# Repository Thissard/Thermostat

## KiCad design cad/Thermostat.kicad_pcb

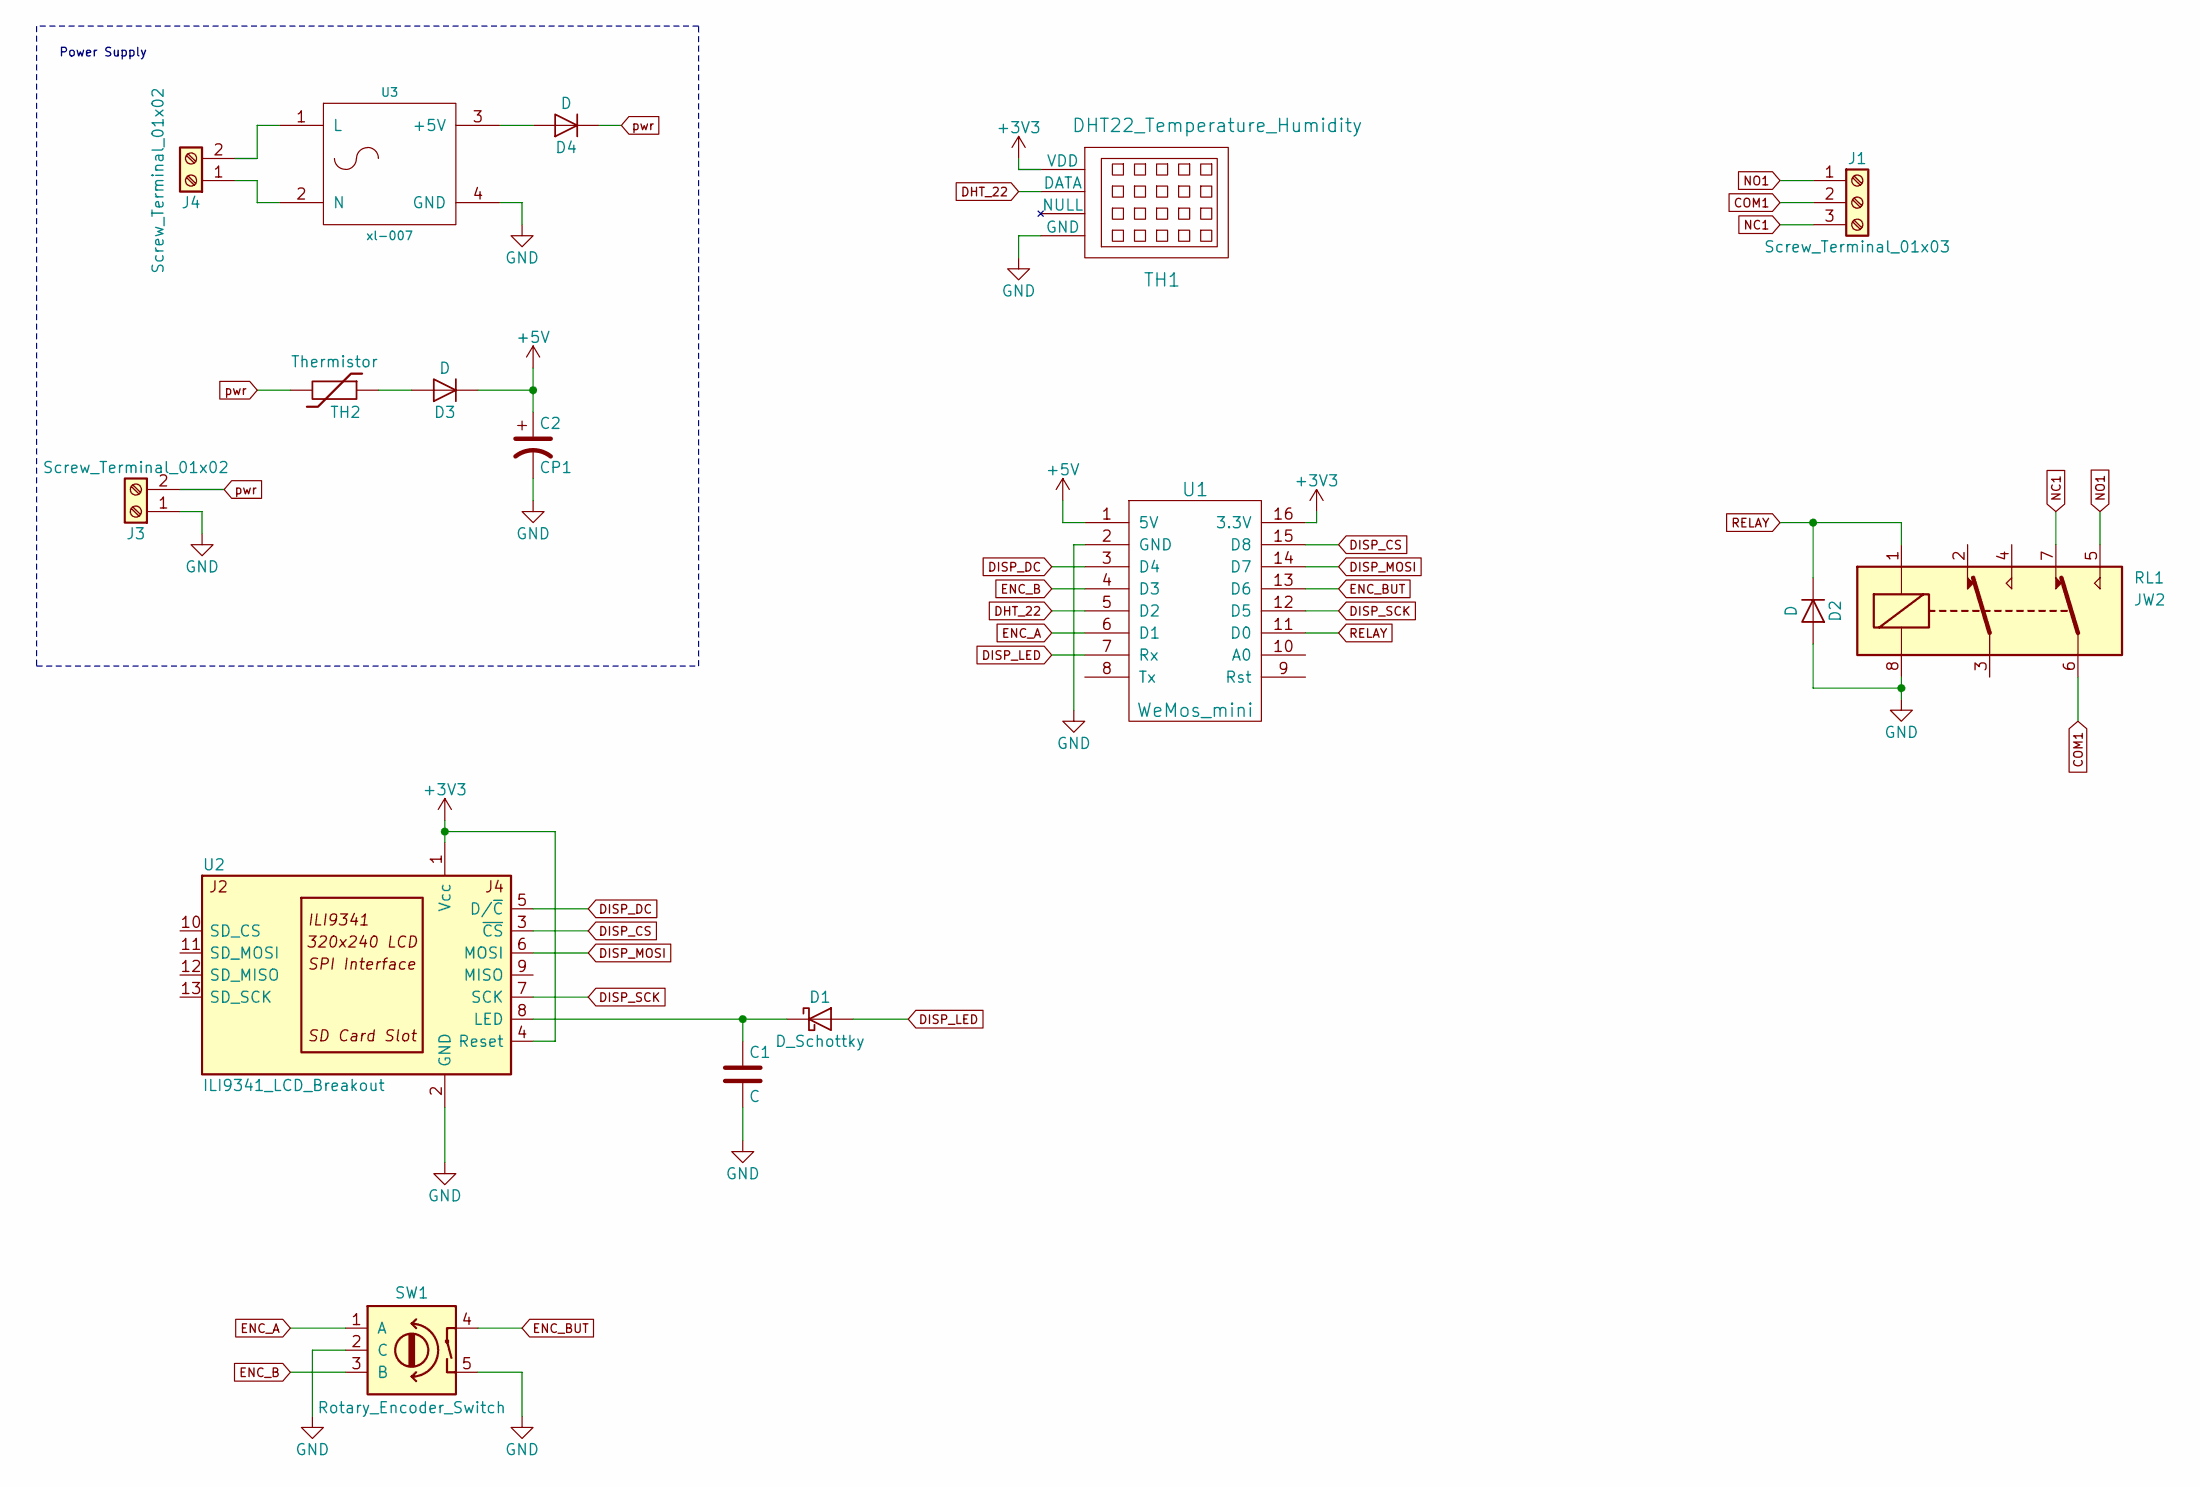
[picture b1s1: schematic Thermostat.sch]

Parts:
C1: C; Resistor_SMD+THTuniversal_0805to2512_HandSoldering
C2: CP1; Resistor_SMD+THTuniversal_0805to2512_HandSoldering
D1: D_Schottky; Resistor_SMD+THTuniversal_0805to2512_HandSoldering
D2, D3, D4: D; Resistor_SMD+THTuniversal_0805to2512_HandSoldering
J1: Screw_Terminal_01x03; PhoenixContact_MC-GF_03x5.08mm_Angled_ThreadedFlange
J3, J4: Screw_Terminal_01x02; PhoenixContact_MC-GF_02x5.08mm_Angled_ThreadedFlange
RL1: JW2; Relay_DPDT_Omron_G5V-2
SW1: Rotary_Encoder_Switch; SF-ROTARY-ENCODER
TH1: DHT22_Temperature_Humidity
TH2: Thermistor; Resistor_SMD+THTuniversal_0805to2512_HandSoldering
U1: WeMos_mini; D1_mini_board
U2: ILI9341_LCD_Breakout; ILI9431 2,8 TFT
U3: xl-007; xl007

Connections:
+3V3: TH1.1 (VDD), U1.16 (3.3V), U2.1 (Vcc), U2.4 (Reset)
+5V: C2.1, D3.1 (K), U1.1 (5V)
COM1: J1.2, RL1.6
DHT_22: TH1.2 (DATA), U1.5 (D2)
DISP_CS: U1.15 (D8), U2.3 (~CS)
DISP_DC: U1.3 (D4), U2.5 (D/~C)
DISP_LED: D1.2 (A), U1.7 (Rx)
DISP_MOSI: U1.14 (D7), U2.6 (MOSI)
DISP_SCK: U1.12 (D5), U2.7 (SCK)
ENC_A: SW1.1 (A), U1.6 (D1)
ENC_B: SW1.3 (B), U1.4 (D3)
ENC_BUT: SW1.4, U1.13 (D6)
GND: C1.2, C2.2, D2.2 (A), J3.1, RL1.8, SW1.2 (C), SW1.5, TH1.4 (GND), U1.2 (GND), U2.2 (GND), U3.4 (GND)
NC1: J1.3, RL1.7
NO1: J1.1, RL1.5
unnamed: C1.1, D1.1 (K), U2.8 (LED)
unnamed: D3.2 (A), TH2.1
unnamed: D4.2 (A), U3.3 (+5V)
unnamed: J4.1, U3.2 (N)
unnamed: J4.2, U3.1 (L)
RELAY: D2.1 (K), RL1.1, U1.11 (D0)
pwr: D4.1 (K), J3.2, TH2.2

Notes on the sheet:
Power Supply

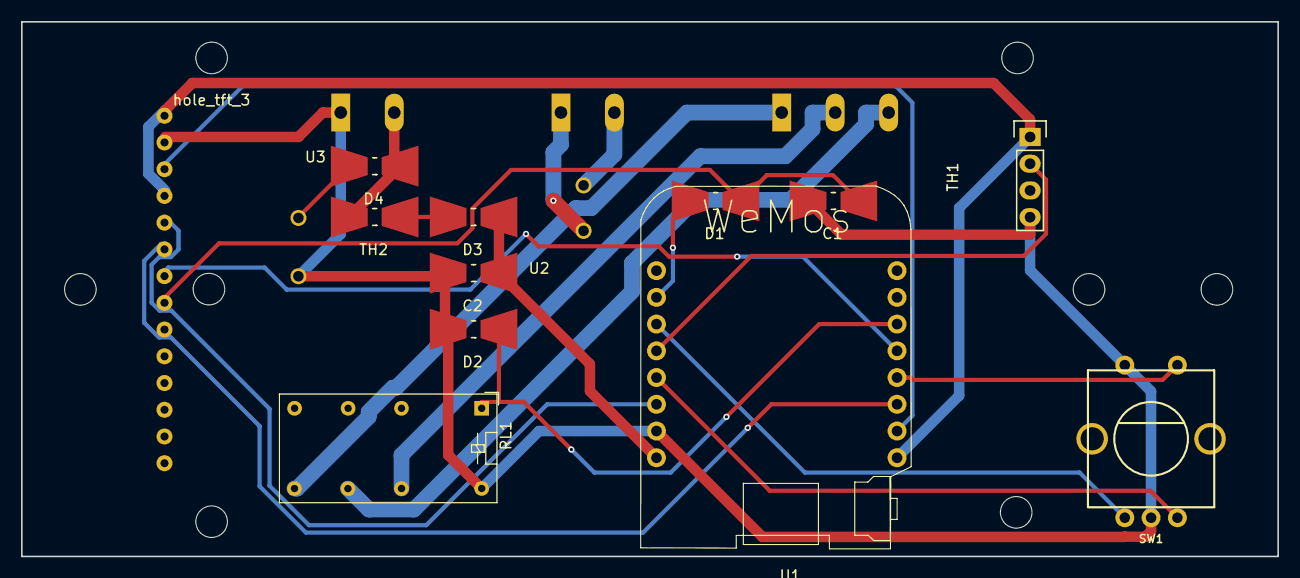
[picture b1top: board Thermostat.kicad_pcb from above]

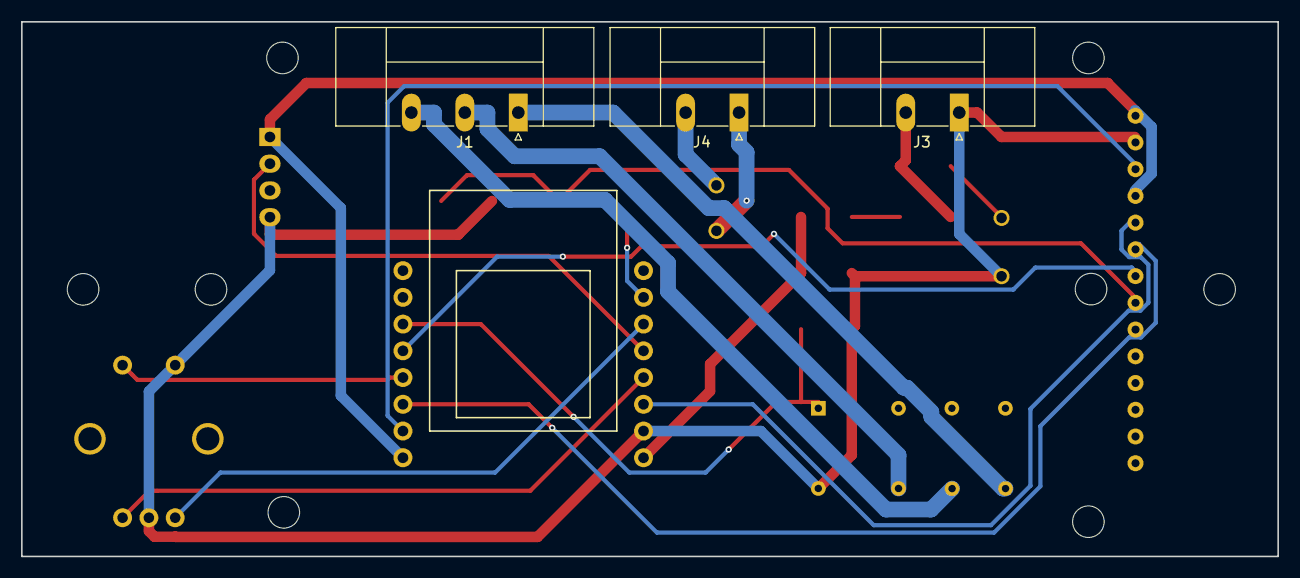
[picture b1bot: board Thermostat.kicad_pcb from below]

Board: 2 copper layers, 119.4 x 50.8 mm, 24 parts (3 on the bottom side), 22 nets.

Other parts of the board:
hole504_1: MountingHole_3mm
hole_503_1, hole_503_2, hole_504_1: MountingHole_3mm
hole_tft_1, hole_tft_2, hole_tft_3, hole_tft_4: MountingHole_3mm

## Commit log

2018-06-25 README.md created online with Bitbucket
2018-06-25 Upload Thermostat library
2018-06-29 Definitive Project and library
2018-06-30 Uploaded UserCommands lib
2018-07-01 Removed library Button and written from scratch button part
2018-07-01 Added UserCommands Fritz Breadoard
2018-07-01 Update UserCommands lib
2018-07-01 DHT test and use
2018-07-01 Task Scheduler implementation
2018-07-01 Inserted Display States
2018-07-02 User Commands Merge test with other libs -- BUTTON NOT WORKING
2018-07-02 Corrected Update of Temperature and Humidity
2018-07-06 UserCommands with interrupt on button
2018-07-06 Still not woriking UserCommands Button
2018-07-08 Removed Button from usercommands in main project kept the metods
2018-07-08 Big Display lib improvements
2018-07-12 Menu page created
2018-07-13 Brightness page created
2018-07-13 Some Fix to display updates behaviour
2018-07-13 Backlight preparation
2018-07-14 Greyscale for brightness
2018-10-06 Fade correction
2018-10-06 Display fade
2018-10-06 Json and filesistem tests added
2018-11-13 Arduino lib backup to prevent damage on updates
2018-11-14 Display upgrade for definitive project Machine states implemented
2018-11-14 Complete navigation + brightness implementation
2018-11-18 Added schematics
2018-11-18 Schematic diode correction
2019-03-03 3dcad
2019-04-26 correction for plastic box design
2019-11-24 Canges due to ESP Core versions Updated schematic PDFs Started MQTT connection
2019-12-09 Removed Serial - Added Telnet
2019-12-15 Json test working
2019-12-27 Json Test read
2019-12-30 Json save and load configuration
2019-12-30 Json integration with full project
2020-03-26 NTP correction and JSON implementation in main Thermostat sketch
2020-03-31 Use Temperature setpoint from chrono programming
2020-03-31 Enumerators and Structures moved in different files easier to manage
2020-04-01 Restored repository
2020-04-03 Fixed Json file bug Read config for graphics Added day progression
2020-04-10 Added Programming page - Only Test
2020-04-13 Programming page and save programmation completed!
2020-04-26 Temperature setpoints added in Display library
2020-05-24 commit test from vscode
2020-05-24 Added page for setpoints programming
